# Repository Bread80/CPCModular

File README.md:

# The CPC Modular

### An Amstrad CPC compatible computer build from modules.

***This project is an unfinished work in progress. It currently has bugs and not all the features have been tested!

The current modules are designed to fit a slightly modified RC2014 Pro backplane. In the text below I shall explain the current status of the project, workarounds needed to get it running and basic build details. Due to the work in progress status of the project this document will be intentionaly terse.

## The modules

### General

The project uses pin header/socket to connect modules within subsystems (the video-RAM subsystem and the IO-sound sub-system). This requires longer pin header than usual.

### Backplane

This is a slightly modified RC2014 Pro backplane. The CPC Modular uses the D8 through D15 lines both within the video-RAM subsystem and the IO-Sound subsystem for local data busses. Therefore:
* You will need to sever the D8 through D15 lines between these sections. 

### CPU

This is a slightly modified RC2014 "Z80 CPU Module". Modification:
* The resistors on the board will need to be replaced with a different value. 2.2k ohm should work nicely.

### ROM

This board contains 512Kb NORFLASH. It includes circuitry to enable the flash to be burned in situ (untested). Config:
* A jumper needs to be installed bridging pin 2 of LK4 and pin 2 of LK5.
* To enable flash burning, install links LK1, LK2 and LK3. Otherwise leave open.
* My notes for writing to the Flash (taken from the schematic file) are:
> !!!
> There is no way to disable memory writes on the standard CPC system. Therefore ANY memory writes which we do to ROM while WRITE_EN is active will also write to RAM.
>
> However, since the ROM maps to any and all memory banks this adds a certain amount of flexibility. Also note that reading from ROM is disabled whilst writing is enabled. This means we can read from the RAM 'underneath' the ROM while the ROM is active.
>
> My recommended programming procedure is to write to the ROM using video RAM addresses, however the ROM could be writting using addresses in bank 1 (&4000-&7fff) if that memory range does not contain meaningful data. (If the data to be written is already in this address range then the programmer can simply read the data (RAM) and then write (ROM) at the same address. Care needs to be taking with commands sent to the ROM though, as these will still trash data underneath).
>
> 1) Read the RAM byte at the address to be programmed.
> 2) Turn on write enable for the ROM
> 3) Write the needed data to ROM.
> 4) Turn off write enable for the ROM
> 5) Write the original data back to ROM.

* The ROM (NORFLASH) can hold up to 31 ROMS plus the firmware ROM. When programming the chip, the Firmware needs to go into slot 31 (starting at address &7c000). BASIC (if installed) needs to go into slot 0 (address &00000). ROM slots are located every &4000 bytes, I.e &00000, &04000, &08000, &0C000, &10000 etc.
* If burning ROMs with the XGPro software:
  1) Use Select IC to select the IC being used (SST39FS040).
  2) Click LOAD toolbar button.
  3) Select the file to load.
  4) File Format: Binary (for .ROM files)
  5) To Region: Default
  6) Load mode: Normal
  7) From File Start Addr: 0000
  8) To Buffer Start Addr: The ROM slot start address (&7C000 for the firmware, &00000 for BASIC)
  9) Clear buffer when loading file: The option 'Clear buffer with default' will *overwrite* any previously loaded data! Use this for the first ROM loaded into XGPro (which will initialise the entire ROM). For all other ROMs select 'Disable' (which will load data only into the selected slot).
  10) Click Okay and verify you file(s) have loaded to the correct address(es) and not been overwritten.
  11) Click PROG (toolbar)
  12) Click Program.

### Video

This board houses the gate array and video output.
* On JP901 the DISPEN and HSYNC signals are swapped compared to those on the equivalent header on the RAM-Control board. This is best fixed on the RAM-Control board (see below).
* The video out circuit is that from the CPC464 but, somehow, I've used component values from the CPC6128 but minus the capacitors on the '6128. This probably doesn't make a significant difference.
* In my testing I'm using the same SCART to HDMI adapter I normally use for Amstrads but here it shows a black and white image, or no image at all. This appears to be an issue between the PSU used by the cable and the adapter. It can be fixed by feeding 5V power to the cable from the CPC Modular board.
* The board includes footprints for both 40007 and 40010 gate arrays (and a 40008 should also work). The footprints overlap to save space. You should be able to include sockets for both by separating the two rows of pins and removing the webbing between them, however, the footprints are a little too close together to do this easily.
* The holes in the footprint for the DIN socket are a little too small.

### RAM-Control

This board houses the link between the video data bus and the CPU data bus, massages the signals to make them suitable for the SRAM memory and houses the optional components required for memories greater than 64k (untested).
* The circuit driving /RAMOE is incorrect. To fix it:
  1) Cut the trace between U192 pins 1 and 13
  2) Cut the trace between U192 pin 11 and U193 pin 1
  3) Install a wire between U192 pin 1 and U195 pin 9
  4) Install a wire between U195 pin 8 and U193 pin 1
* As noted for the video board, the DISPEN and HSYNC pins are swapped on the connectors between the boards. To fix this:
  1) Cut the trace between J1 pin 2 and J2 pin 2
  2) Cut the trace between J1 pin 3 and J2 pin 3
  3) Install a wire between J1 pin 2 and J2 pin 3
  4) Install a wire between J1 pin 3 and J2 pin 2
* To use <= 64k RAM install links LK5, LK6 and LK7. If so DO NOT insert IC118 and U194
* To use > 64k RAM leave LK5, LK6, LK7 open and install IC118 and U194. IC118 is a standard Amstrad HAL/PAL.

The correct circuit to drive /RAMOE is:
```
XCPU_AD-----|
            |--
/XCPU_AD--     AND---/ROMOE
          OR---
/RAMRD----
```
In text form:
`/ROMOE := XCPU_AD AND (/XCPU_AD OR /RAMRD)`

XCPU_AD can be sourced from U195 pin 8.

### RAM

This board houses the 6845 CRTC, address multiplexers and 512Kb SRAM. There are no issues here, and no config is necessary.
* Headers can be installed for CURSOR and LPEN if required. They probably aren't.

### IO

This board houses the 8255 PIO and tape interface. Solder links and jumpers are installed to make the I/O address configurable:
* The board was designed such that the IO board could be mounted 'above/in front of' it but the relay is too tall to allow that. Thus: I'd recommend you mount J902 on the rear of the board (this is the connector to the Sound board).
* On the rear of the board find the solder links just above the address pins. On each link you need to solder the 'high' address pad (labelled A7(sic) to A15) to the central pad. The 'low' address pads (A0..A7) must NOT connected to the centre pads.
* On the front of the board find the links located between  U1 and D302. You need to jumper the 'low' link (to the centre pin) for the link labelled A3, and the high link (to the centre pin) for the others (A2, A4, A5, A6, A7).
* Find the links located between C315 and J901. The configure which signals are directed to the jack sockets and which are directed to the backplane. The recommended setup is:
  1) Install links between the INT(ernal) and middle pins for TO, TI and /MO (Tape Out, Tape In and Motor).
  2) Leave the /EXP link open.
* J901 allows access to various 8255 input signals. By default all these lines have pull-ups and can be ignored.
  1) RG0, RG1, RG2 are the region setting.
  2) VHz is the 50Hz/60Hz setting for video output.
  3) /EXP is the /EXP signal.
  4) PBSY is Printer Busy signal. The CPC Modular does not include a parallel port. This signal can be used for expansion if desired.
* J1, J2 and J3 are the tape I/O jacks. J3 (Motor) should be a 2.5mm jack socket but the footprint is for a 3.5mm socket.

### Sound

This board houses the AY-3-8910 sound generator and associated outputs, plus the keyboard and joystick connectors.
* As noted for the IO board: You should mount the inter-board connector (J902) on the top of this board, not the rear as shown in the silkscreen.
* The board has the ability to use an on-board oscillator for the AY's clock input. In the CPC Modular: Omit X1 and install a jumper at the CLK2 end of JP3 (which configures the board to use the clock signal from the gate array send through the backplane).
* The jumpers above J103 (audio out jack) allow various audio signals to be sent to a variety of backplane pins. In most cases these can be left open. Note that some of the settings may conflict with tape signals routed via the backplane on the IO board.
* If an audio jack is installed the LEFT and RIGHT signals will NOT be sent to the backplane (if configured to do so - see previous item). However the audio MIX will still be sent (if configured so).
* CP2 is the keyboard connector. This uses the same pinout as the original Amstrad CPC464 (PCB keyboard).
* J102 is the joystick connector. The connector here is mounted a little too 'inboard' and could short a PCB in the next socket.

## Links

HAL/PAL:
* Code for original: https://www.cpcwiki.eu/index.php/PAL16L8
* WiP replacement: https://github.com/Bread80/GreenHAL
* WiP replacement: https://www.cpcwiki.eu/forum/index.php?msg=231084

Gate Array:
* WiP FPGA based replacement: https://github.com/codedchip/AMSGateArray

ROM Images:
https://www.cpcwiki.eu/index.php/ROM_List

## Licence, Copyright and Contact Details

* Licence: CERN-OHL-P
* Copyright © Mike Sutton, 2023
* Website: https://bread80.com
* Social media (Mastodon): https://mstdn.social/@bread80

## Notes

There's nothing useful beyond here. But if you've made it this far you'll probably keep going anyway.

Signal lines
------------

Signals through RC2014 backplane
====

Common (whole board)
----
TX/RX=Sound (Left, right) **Jumpered (optional)
USR1=ROMDIS
USR2=/ROMEN
USR3=VSYNC (Video to IO)
USR4=<unusable>

/WAIT=READY (it already is!)
CLOCK2=/CPU_ADDR (RAM board; 1MHz clock for sound)
RX2=Tape in **Jumpered (optional)
TX2=Tape out **Jumpered (optional)
USR5=RAMDIS ***MOVED***
USR6=/RAMRD ***MOVED***
USR7=Motor **Jumpered (optional)

Video section
----
D8-D15=Video bus

IO Section
----
D8-D15=IO bus
???Control signals???

Signals through inter-board connectors
====

Video board to RAM Control board
----
Position=Top row of holes @ 45.72mm above centre of basic RC2014 header pins,
 Leftmost pins = mid-point between A9 and A8 
 Pin 1 to the right
1 GND
2 HSYNC (in)
3 DISPEN (in)
4 GND
5 /RAS (out)
6 /CAS (out)
7 /MWE (out)
8 /CCLK (out)
9 /244EN (out)
10 GND

RAM Control board to RAM board
----
Position=Top row of holes @ 43.18mm above centre of extended header pins, 
 Leftmost pins = mid-point between D2 and D3 pins
 Pin 1 to the left, all grounds on topmost row.
1=GND
2=HSYNC (in)
3=DISPEN (in)
4=/CCLK (out)
5=/XCPU_ADDR (out)
6=/RAMCS (out)
7=GND
8=/RAMOE (out)
9=GND
10=/RAMWE (out)
11=RAMA14 (out)
12=RAMA15 (out)
13=RAMA16 (out)
14=RAMA17 (out)
15=GND
16=RAMA18 (out)

IO board to Sound board
----
1=GND
2=BC1
3=BDIR
4=PC0
5=PC1
6=PC2
7=PC3
8=GND

Amstrad/MX4 pinout

Expansion  RAM Ctrl	RAM	Video	IO	AY	DDI
---
GND			
  SOUND							Y
A15			Y		Y	Y
  A14		Y		Y	Y
A13					Y
  A12				Y
A11					Y			Y
  A10				Y					Y
A9					Y			Y
  A8				Y			Y		Y
A7					Y					Y
  A6				Y
A5					Y
  A4				Y
A3					Y
  A2				Y
A1					Y			
  A0				Y					Y

D7			Y		Y			Y
  D6		Y		Y			Y
D5			Y		Y			Y
  D4		Y		Y			Y
D3			Y		Y			Y
  D2		Y		Y			Y
D1			Y		Y			Y
  D0		Y		Y			Y
					(CRTC)
VCC
  MREQ					Y
M1						Y		Y
  RFSH
IORQ				Y	Y		Y		Y
  RD				Y	Y		Y		Y
WR			Y		Y			Y		Y
  HALT
INT						Y
  NMI
BUSRQ
  BUSAK
READY		Y			Y
  BRST
RSET		Y?			Y?		Y?	Y?	Y?
  ROMEN					Y
ROMDIS		Y
  RAMRD		Y			Y
RAMDIS		
  CURSOR			Y
LPEN				Y
  EXP							Y		Y
GND
  CLK4					Y				Y

Extra (Video-RAM):
RD7..RD0	Y		Y	Y
RAS			Y			Y
CAS			Y			Y
MWE			Y			Y
244EN		Y			Y
XCPU_AD(?)	Y		Y
RAMCS		Y		Y
RAMOE		Y		Y
RAMWE		Y		Y	
RAMA18..RAMA14  Y	Y
HSYNC				Y	Y
DISPEN				Y	Y
CCLK				Y	Y
(24 lines)

Extra (Video-RAM and IO-Sound):
CPU_ADDR(1MHz) Y		Y		Y
VSYNC				Y	Y		Y
(2 lines)

Extra (IO-Sound):
PA7..PA0						Y	Y
MOTOR							Y
CASRD							Y
CASWR							Y
PRINTBUSY						(Y)
BC1								Y	Y
BDIR							Y	Y
PC3..PC0						Y	Y
LEFT								Y
RIGHT								Y
(20 lines)

Disc:
Approx 14 lines required internally

Video/RAM: 50 + 24 + 2 = 76 lines! total. Less un-needed: 69 total (70 plus one spare!)
IO/Sound: 50 + 20 + 2 = 72 lines total. Less un-needed: 50 total (inc a couple of spares)
Disc: 50 + 14 = 64 lines total

Notes:
76 pin edge connector: board width = 99.06mm

Boards:
MX4 section:
CPU
ROM
Spare(s)
RC2014
Edge connector

Video section (gate array):
Video
RAM
RAM Control

Video section (RP2040):
Video
Signals
RAM
Transceiver

Disc Section:
Controller
Connectors/Buffers

IO Sound section:
PPI
AY
Tape
Audio amp/mixer

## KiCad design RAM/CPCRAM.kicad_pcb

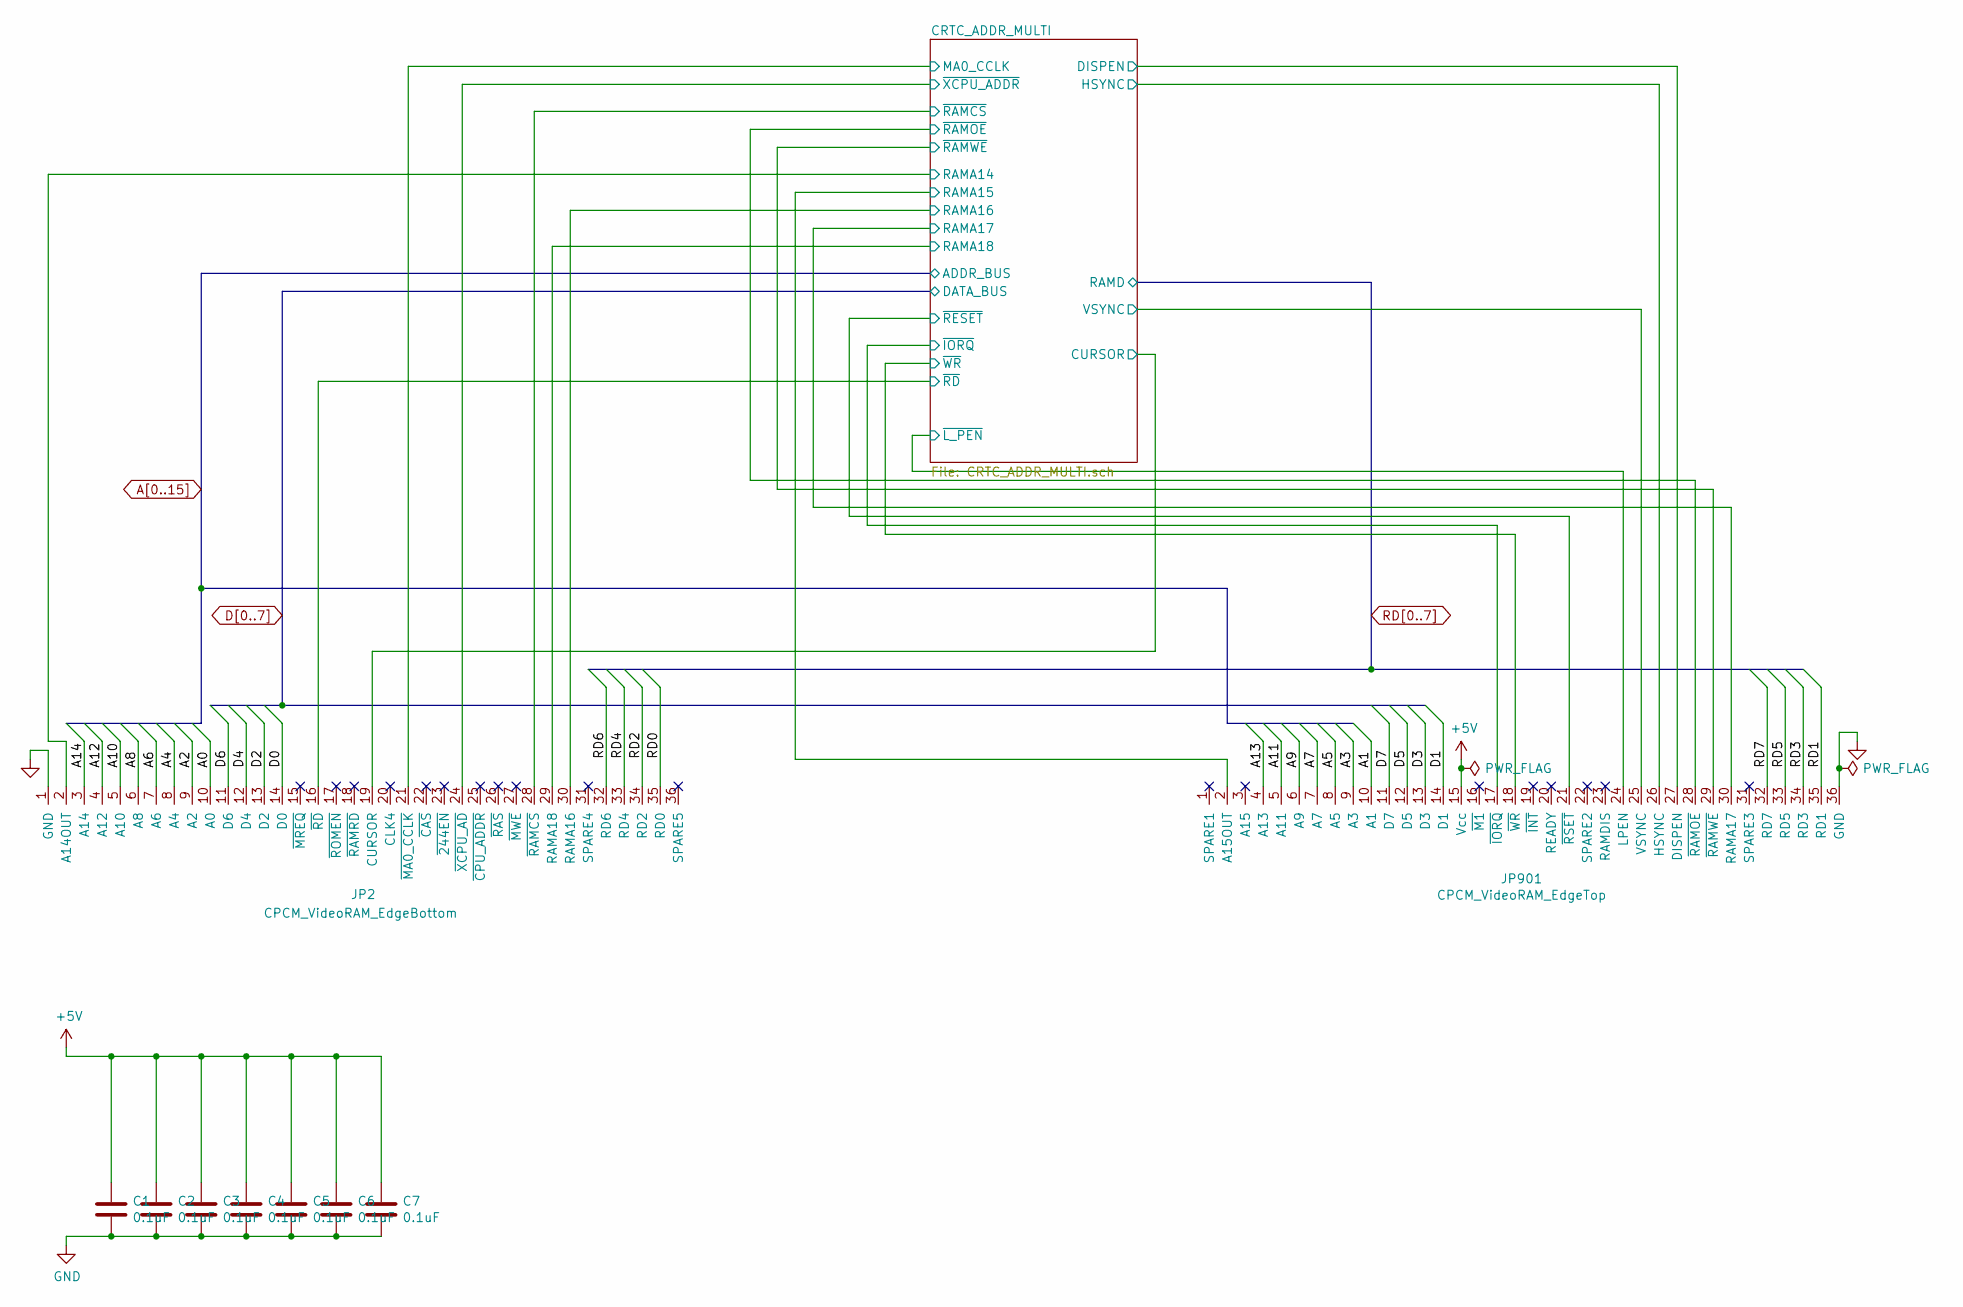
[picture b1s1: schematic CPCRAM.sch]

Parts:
C1, C2, C3, C4, C5, C6, C7: 0.1uF; C_Disc_D3.0mm_W2.0mm_P2.50mm
JP2: CPCM_VideoRAM_EdgeBottom; Edge36_2.54PS
JP901: CPCM_VideoRAM_EdgeTop; Edge36_2.54PS

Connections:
+5V: C1.1, C2.1, C3.1, C4.1, C5.1, C6.1, C7.1, JP901.15 (Vcc); also elsewhere on the board
/CRTC_ADDR_MULTI/A14OUT: JP2.2 (A14OUT); also elsewhere on the board
/CRTC_ADDR_MULTI/A15OUT: JP901.2 (A15OUT); also elsewhere on the board
/CRTC_ADDR_MULTI/CURSOR: JP2.19 (CURSOR); also elsewhere on the board
/CRTC_ADDR_MULTI/DISPEN: JP901.27 (DISPEN); also elsewhere on the board
/CRTC_ADDR_MULTI/HSYNC: JP901.26 (HSYNC); also elsewhere on the board
/CRTC_ADDR_MULTI/MA0_CCLK: JP2.21 (~MA0_CCLK); also elsewhere on the board
/CRTC_ADDR_MULTI/VSYNC: JP901.25 (VSYNC); also elsewhere on the board
/CRTC_ADDR_MULTI/~IORQ: JP901.17 (~IORQ); also elsewhere on the board
/CRTC_ADDR_MULTI/~L_PEN: JP901.24 (LPEN); also elsewhere on the board
/CRTC_ADDR_MULTI/~RAMCS: JP2.28 (~RAMCS); also elsewhere on the board
/CRTC_ADDR_MULTI/~RAMOE: JP901.28 (~RAMOE); also elsewhere on the board
/CRTC_ADDR_MULTI/~RAMWE: JP901.29 (~RAMWE); also elsewhere on the board
/CRTC_ADDR_MULTI/~RD: JP2.16 (~RD); also elsewhere on the board
/CRTC_ADDR_MULTI/~RESET: JP901.21 (~RSET); also elsewhere on the board
/CRTC_ADDR_MULTI/~WR: JP901.18 (~WR); also elsewhere on the board
/CRTC_ADDR_MULTI/~XCPU_ADDR: JP2.24 (~XCPU_AD); also elsewhere on the board
A0: JP2.10 (A0); also elsewhere on the board
A1: JP901.10 (A1); also elsewhere on the board
A2: JP2.9 (A2); also elsewhere on the board
A3: JP901.9 (A3); also elsewhere on the board
A4: JP2.8 (A4); also elsewhere on the board
A5: JP901.8 (A5); also elsewhere on the board
A6: JP2.7 (A6); also elsewhere on the board
A7: JP901.7 (A7); also elsewhere on the board
A8: JP2.6 (A8); also elsewhere on the board
A9: JP901.6 (A9); also elsewhere on the board
A10: JP2.5 (A10); also elsewhere on the board
A11: JP901.5 (A11); also elsewhere on the board
A12: JP2.4 (A12); also elsewhere on the board
A13: JP901.4 (A13); also elsewhere on the board
A14: JP2.3 (A14); also elsewhere on the board
D0: JP2.14 (D0); also elsewhere on the board
D1: JP901.14 (D1); also elsewhere on the board
D2: JP2.13 (D2); also elsewhere on the board
D3: JP901.13 (D3); also elsewhere on the board
D4: JP2.12 (D4); also elsewhere on the board
D5: JP901.12 (D5); also elsewhere on the board
D6: JP2.11 (D6); also elsewhere on the board
D7: JP901.11 (D7); also elsewhere on the board
GND: C1.2, C2.2, C3.2, C4.2, C5.2, C6.2, C7.2, JP2.1 (GND), JP901.36 (GND); also elsewhere on the board
RAMA16: JP2.30 (RAMA16); also elsewhere on the board
RAMA17: JP901.30 (RAMA17); also elsewhere on the board
RAMA18: JP2.29 (RAMA18); also elsewhere on the board
RD0: JP2.35 (RD0); also elsewhere on the board
RD1: JP901.35 (RD1); also elsewhere on the board
RD2: JP2.34 (RD2); also elsewhere on the board
RD3: JP901.34 (RD3); also elsewhere on the board
RD4: JP2.33 (RD4); also elsewhere on the board
RD5: JP901.33 (RD5); also elsewhere on the board
RD6: JP2.32 (RD6); also elsewhere on the board
RD7: JP901.32 (RD7); also elsewhere on the board

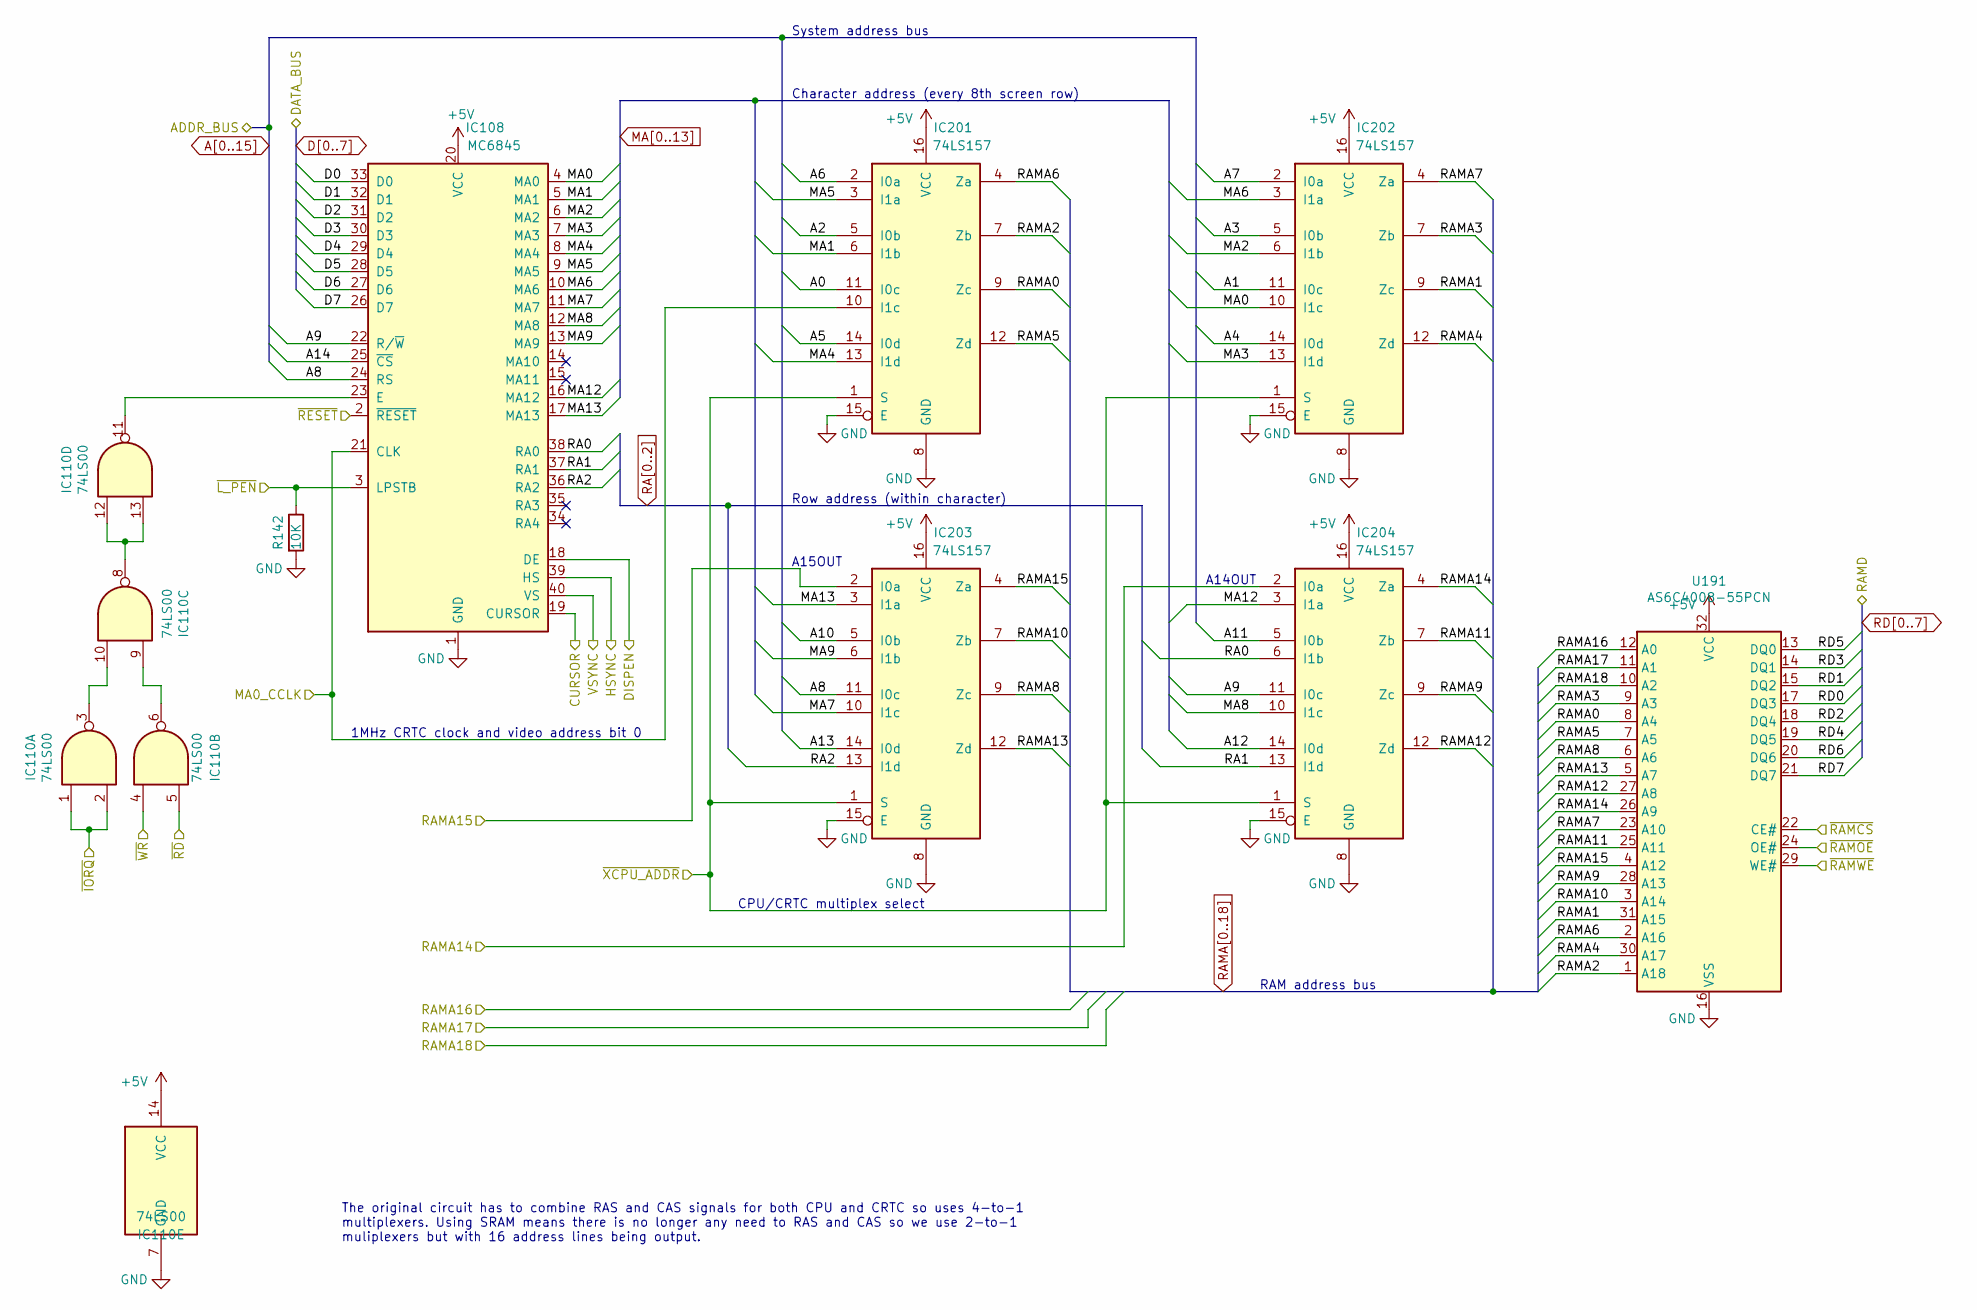
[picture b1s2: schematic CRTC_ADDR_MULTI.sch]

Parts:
IC108: MC6845; DIP-40_W15.24mm_Socket
IC110: 74LS00; DIP-14_W7.62mm_Socket
IC201, IC202, IC203, IC204: 74LS157; DIP-16_W7.62mm_Socket
R142: 10K; R_Axial_DIN0207_L6.3mm_D2.5mm_P7.62mm_Horizontal
U191: AS6C4008-55PCN; DIP-32_W15.24mm

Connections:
+5V: IC108.20 (VCC), IC110.14 (VCC), IC201.16 (VCC), IC202.16 (VCC), IC203.16 (VCC), IC204.16 (VCC), U191.32 (VCC); also elsewhere on the board
/CRTC_ADDR_MULTI/A14OUT: IC204.2 (I0a); also elsewhere on the board
/CRTC_ADDR_MULTI/A15OUT: IC203.2 (I0a); also elsewhere on the board
/CRTC_ADDR_MULTI/CURSOR: IC108.19 (CURSOR); also elsewhere on the board
/CRTC_ADDR_MULTI/DISPEN: IC108.18 (DE); also elsewhere on the board
/CRTC_ADDR_MULTI/HSYNC: IC108.39 (HS); also elsewhere on the board
/CRTC_ADDR_MULTI/MA0_CCLK: IC108.21 (CLK), IC201.10 (I1c); also elsewhere on the board
/CRTC_ADDR_MULTI/VSYNC: IC108.40 (VS); also elsewhere on the board
/CRTC_ADDR_MULTI/~IORQ: IC110.1, IC110.2; also elsewhere on the board
/CRTC_ADDR_MULTI/~L_PEN: IC108.3 (LPSTB), R142.1; also elsewhere on the board
/CRTC_ADDR_MULTI/~RAMCS: U191.22 (CE#); also elsewhere on the board
/CRTC_ADDR_MULTI/~RAMOE: U191.24 (OE#); also elsewhere on the board
/CRTC_ADDR_MULTI/~RAMWE: U191.29 (WE#); also elsewhere on the board
/CRTC_ADDR_MULTI/~RD: IC110.5; also elsewhere on the board
/CRTC_ADDR_MULTI/~RESET: IC108.2 (~RESET); also elsewhere on the board
/CRTC_ADDR_MULTI/~WR: IC110.4; also elsewhere on the board
/CRTC_ADDR_MULTI/~XCPU_ADDR: IC201.1 (S), IC202.1 (S), IC203.1 (S), IC204.1 (S); also elsewhere on the board
A0: IC201.11 (I0c); also elsewhere on the board
A1: IC202.11 (I0c); also elsewhere on the board
A2: IC201.5 (I0b); also elsewhere on the board
A3: IC202.5 (I0b); also elsewhere on the board
A4: IC202.14 (I0d); also elsewhere on the board
A5: IC201.14 (I0d); also elsewhere on the board
A6: IC201.2 (I0a); also elsewhere on the board
A7: IC202.2 (I0a); also elsewhere on the board
A8: IC108.24 (RS), IC203.11 (I0c); also elsewhere on the board
A9: IC108.22 (R/~W), IC204.11 (I0c); also elsewhere on the board
A10: IC203.5 (I0b); also elsewhere on the board
A11: IC204.5 (I0b); also elsewhere on the board
A12: IC204.14 (I0d); also elsewhere on the board
A13: IC203.14 (I0d); also elsewhere on the board
A14: IC108.25 (~CS); also elsewhere on the board
D0: IC108.33 (D0); also elsewhere on the board
D1: IC108.32 (D1); also elsewhere on the board
D2: IC108.31 (D2); also elsewhere on the board
D3: IC108.30 (D3); also elsewhere on the board
D4: IC108.29 (D4); also elsewhere on the board
D5: IC108.28 (D5); also elsewhere on the board
D6: IC108.27 (D6); also elsewhere on the board
D7: IC108.26 (D7); also elsewhere on the board
GND: IC108.1 (GND), IC110.7 (GND), IC201.8 (GND), IC201.15 (E), IC202.8 (GND), IC202.15 (E), IC203.8 (GND), IC203.15 (E), IC204.8 (GND), IC204.15 (E), R142.2, U191.16 (VSS); also elsewhere on the board
MA0: IC108.4 (MA0), IC202.10 (I1c)
MA1: IC108.5 (MA1), IC201.6 (I1b)
MA2: IC108.6 (MA2), IC202.6 (I1b)
MA3: IC108.7 (MA3), IC202.13 (I1d)
MA4: IC108.8 (MA4), IC201.13 (I1d)
MA5: IC108.9 (MA5), IC201.3 (I1a)
MA6: IC108.10 (MA6), IC202.3 (I1a)
MA7: IC108.11 (MA7), IC203.10 (I1c)
MA8: IC108.12 (MA8), IC204.10 (I1c)
MA9: IC108.13 (MA9), IC203.6 (I1b)
MA12: IC108.16 (MA12), IC204.3 (I1a)
MA13: IC108.17 (MA13), IC203.3 (I1a)
unnamed: IC108.23 (E), IC110.11
unnamed: IC110.6, IC110.9
unnamed: IC110.3, IC110.10
unnamed: IC110.8, IC110.12, IC110.13
RA0: IC108.38 (RA0), IC204.6 (I1b)
RA1: IC108.37 (RA1), IC204.13 (I1d)
RA2: IC108.36 (RA2), IC203.13 (I1d)
RAMA0: IC201.9 (Zc), U191.8 (A4)
RAMA1: IC202.9 (Zc), U191.31 (A15)
RAMA2: IC201.7 (Zb), U191.1 (A18)
RAMA3: IC202.7 (Zb), U191.9 (A3)
RAMA4: IC202.12 (Zd), U191.30 (A17)
RAMA5: IC201.12 (Zd), U191.7 (A5)
RAMA6: IC201.4 (Za), U191.2 (A16)
RAMA7: IC202.4 (Za), U191.23 (A10)
RAMA8: IC203.9 (Zc), U191.6 (A6)
RAMA9: IC204.9 (Zc), U191.28 (A13)
RAMA10: IC203.7 (Zb), U191.3 (A14)
RAMA11: IC204.7 (Zb), U191.25 (A11)
RAMA12: IC204.12 (Zd), U191.27 (A8)
RAMA13: IC203.12 (Zd), U191.5 (A7)
RAMA14: IC204.4 (Za), U191.26 (A9)
RAMA15: IC203.4 (Za), U191.4 (A12)
RAMA16: U191.12 (A0); also elsewhere on the board
RAMA17: U191.11 (A1); also elsewhere on the board
RAMA18: U191.10 (A2); also elsewhere on the board
RD0: U191.17 (DQ3); also elsewhere on the board
RD1: U191.15 (DQ2); also elsewhere on the board
RD2: U191.18 (DQ4); also elsewhere on the board
RD3: U191.14 (DQ1); also elsewhere on the board
RD4: U191.19 (DQ5); also elsewhere on the board
RD5: U191.13 (DQ0); also elsewhere on the board
RD6: U191.20 (DQ6); also elsewhere on the board
RD7: U191.21 (DQ7); also elsewhere on the board

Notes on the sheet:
The original circuit has to combine RAS and CAS signals for both CPU and CRTC so uses 4-to-1 multiplexers. Using SRAM means there is no longer any need to RAS and CAS so we use 2-to-1 muliplexers but with 16 address lines being output.
Row address (within character)
Character address (every 8th screen row)
CPU/CRTC multiplex select
1MHz CRTC clock and video address bit 0
System address bus
A14OUT
A15OUT
RAM address bus

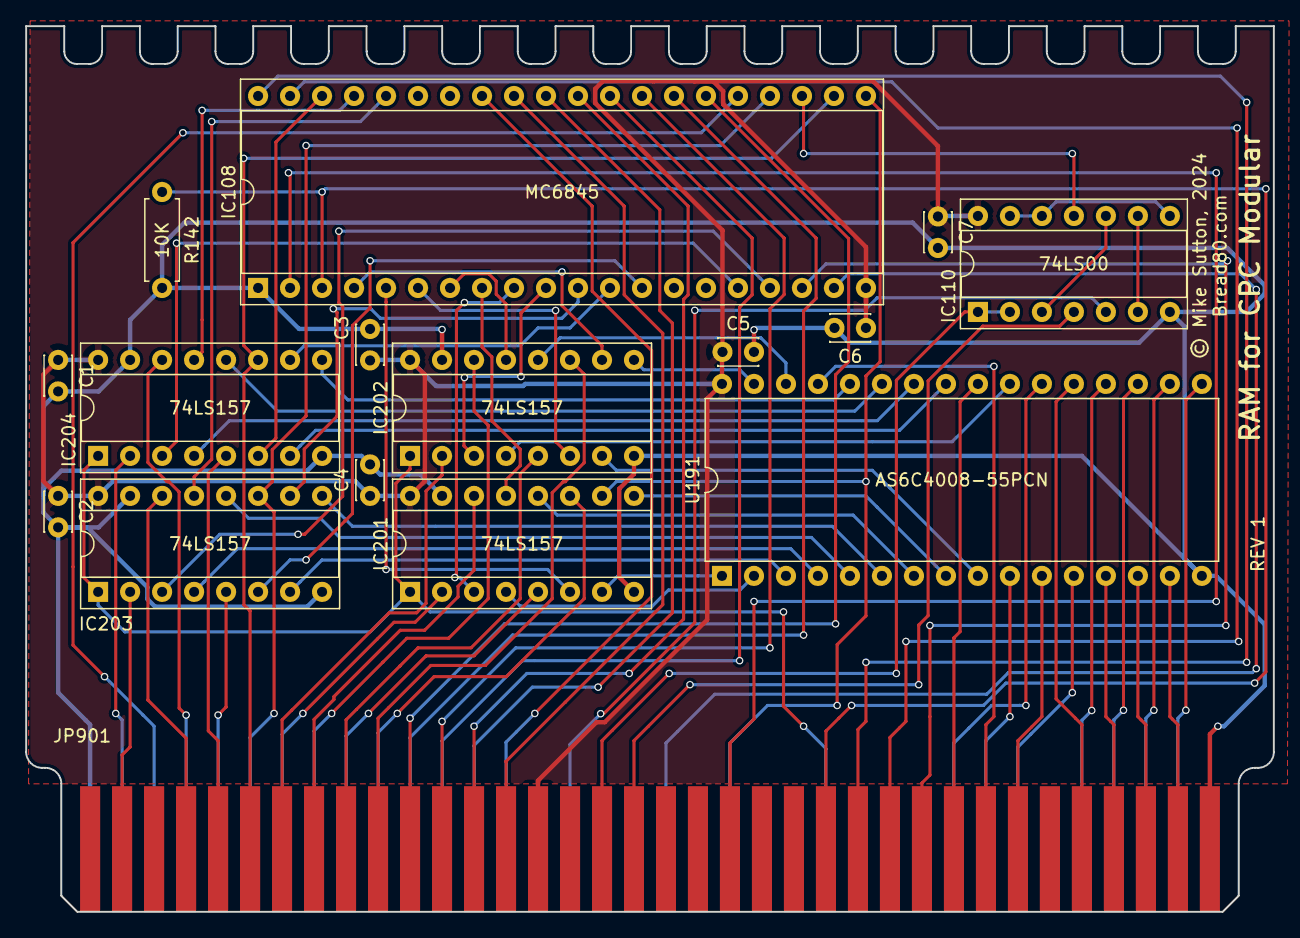
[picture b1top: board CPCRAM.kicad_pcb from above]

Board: 2 copper layers, 99.1 x 70.3 mm, 17 parts (1 on the bottom side), 87 nets.

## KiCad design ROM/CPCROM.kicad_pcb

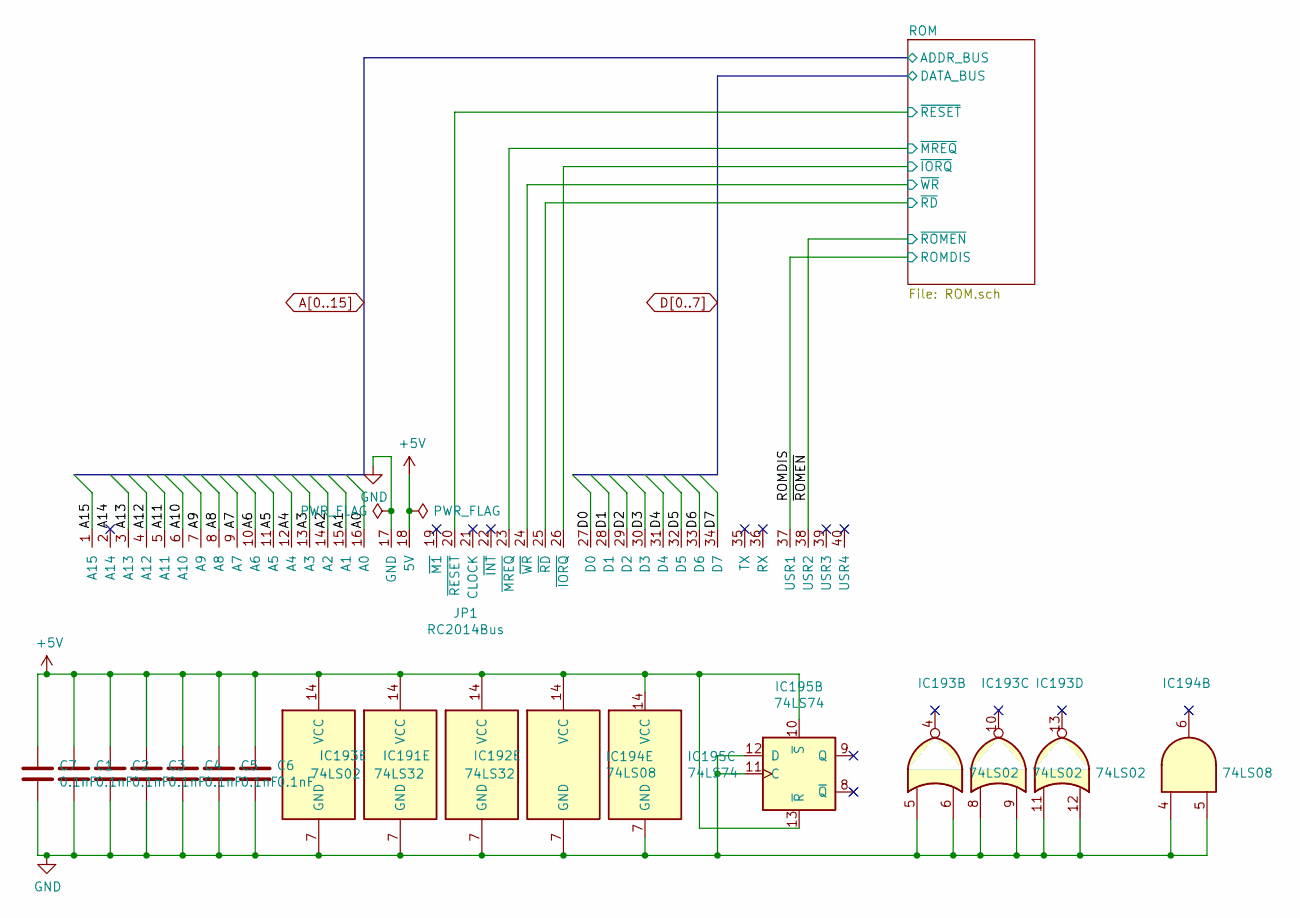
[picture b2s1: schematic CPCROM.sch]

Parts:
C1, C2, C3, C4, C5, C6, C7: 0.1nF; C_Disc_D3.0mm_W2.0mm_P2.50mm
IC191, IC192: 74LS32
IC193: 74LS02
IC194: 74LS08
IC195: 74LS74
JP1: RC2014Bus; PinHeader_1x40_P2.54mm_Vertical

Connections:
/RAMDIS: JP1.6 (A10); also elsewhere on the board
/ROM/~WRITE_EN: IC195.8 (~Q); also elsewhere on the board
/ROMDIS: JP1.8 (A8); also elsewhere on the board
/~IORQ: JP1.20 (~RESET); also elsewhere on the board
/~MREQ: JP1.23 (~MREQ); also elsewhere on the board
/~RD: JP1.19 (~M1); also elsewhere on the board
/~RESET: JP1.10 (A6); also elsewhere on the board
/~ROMEN: JP1.9 (A7); also elsewhere on the board
A0: JP1.33 (D6); also elsewhere on the board
A1: JP1.34 (D7); also elsewhere on the board
A2: JP1.35 (TX); also elsewhere on the board
A3: JP1.36 (RX); also elsewhere on the board
A4: JP1.37 (USR1); also elsewhere on the board
A5: JP1.38 (USR2); also elsewhere on the board
A6: JP1.39 (USR3); also elsewhere on the board
A7: JP1.40 (USR4); also elsewhere on the board
A8: JP1.41; also elsewhere on the board
A9: JP1.42; also elsewhere on the board
A10: JP1.43; also elsewhere on the board
A11: JP1.44; also elsewhere on the board
A12: JP1.45; also elsewhere on the board
A13: JP1.46; also elsewhere on the board
D0: JP1.25 (~RD); also elsewhere on the board
D1: JP1.26 (~IORQ); also elsewhere on the board
D2: JP1.27 (D0); also elsewhere on the board
D3: JP1.28 (D1); also elsewhere on the board
D4: JP1.29 (D2); also elsewhere on the board
D5: JP1.30 (D3); also elsewhere on the board
D6: JP1.31 (D4); also elsewhere on the board
D7: JP1.32 (D5); also elsewhere on the board
unnamed 34: IC193.4; also elsewhere on the board
unnamed 36: IC193.10; also elsewhere on the board
unnamed 51: IC194.6; also elsewhere on the board
WRITE_EN: IC195.9 (Q); also elsewhere on the board

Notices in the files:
Backplane/Backplane.kicad_pcb:
© Mike Sutton, 2024  -  Bread80.com
